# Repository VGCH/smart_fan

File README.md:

## Проект домашней автоматизации вытяжной вентиляции 

Принципиальная схема

Полное описание в статье на Хабр

[Ссылка на статью ](https://habr.com/ru/articles/823752/)

Если данный проект был вам полезен, то вы можете задонатить разработчику на кофе. 

[Ссылка на Boosty ](https://boosty.to/cyberex_tech)

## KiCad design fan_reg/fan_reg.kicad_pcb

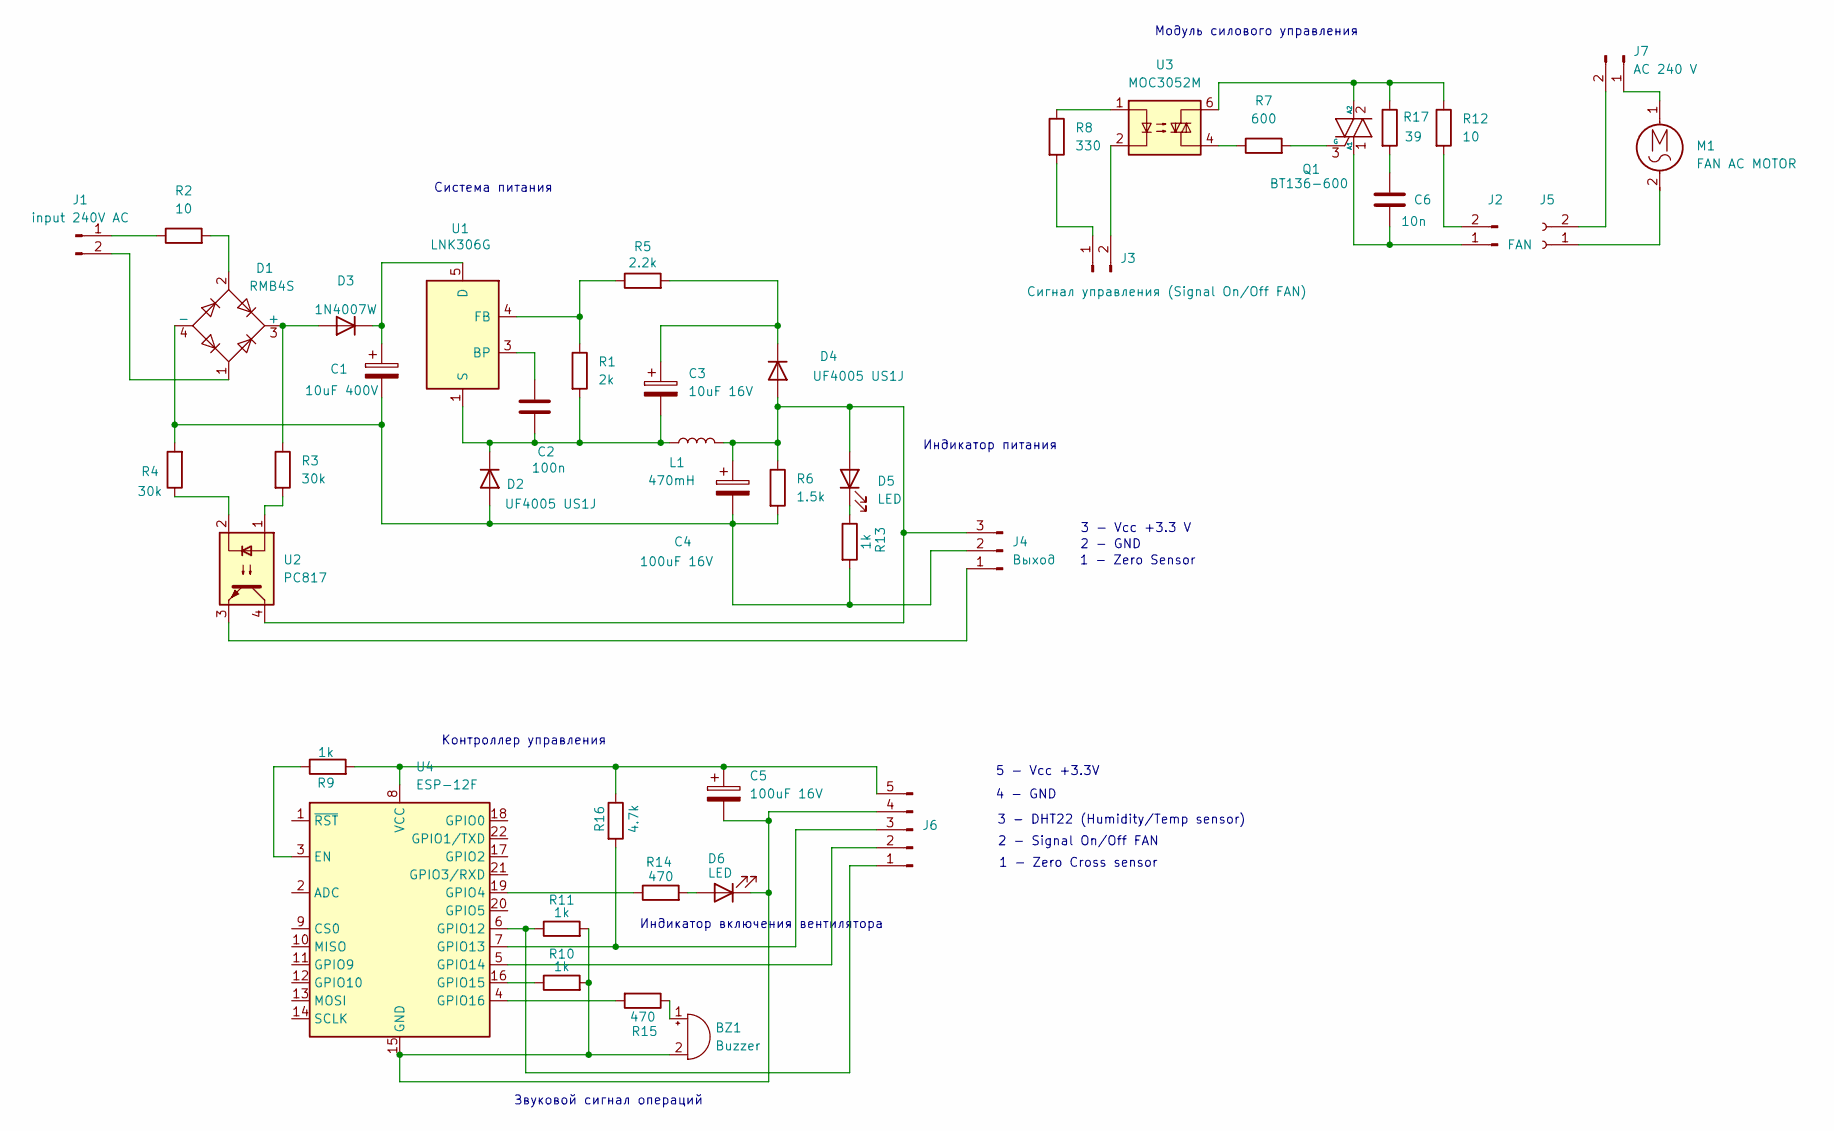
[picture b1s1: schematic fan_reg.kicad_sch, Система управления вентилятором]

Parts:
BZ1: Buzzer; MagneticBuzzer_PUI_AT-0927-TT-6-R
C1: 10uF 400V; CP_Radial_D8.0mm_P3.80mm
C2: 100n; C_1206_3216Metric
C3: 10uF 16V; CP_Elec_5x5.4
C4, C5: 100uF 16V; CP_Elec_5x5.4
C6: 10n; C_1206_3216Metric
D1: RMB4S; TO-269AA
D2, D4: UF4005 US1J; D_MELF
D3: 1N4007W; D_MELF
D5, D6: LED; LED_1206_3216Metric
J1: input 240V AC; TerminalBlock_bornier-2_P5.08mm
J2: FAN; TerminalBlock_bornier-2_P5.08mm
J3: Сигнал управления (Signal On/Off FAN); TerminalBlock_bornier-2_P5.08mm
J4: Выход; TerminalBlock_bornier-3_P5.08mm
J5: (no value)
J6: TerminalBlock_bornier-5_P5.08mm
J7: AC 240 V
L1: 470mH; L_Axial_L9.5mm_D4.0mm_P2.54mm_Vertical_Fastron_SMCC
M1: FAN AC MOTOR
Q1: BT136-600; TO-252-2
R1: 2k; R_0805_2012Metric
R2, R12: 10; R_1206_3216Metric
R3, R4: 30k; R_1206_3216Metric
R5: 2.2k; R_0805_2012Metric
R6: 1.5k; R_0805_2012Metric
R7: 600; R_0805_2012Metric
R8: 330; R_0805_2012Metric
R9, R10, R11, R13: 1k; R_0805_2012Metric
R14, R15: 470; R_0805_2012Metric
R16: 4.7k; R_0805_2012Metric
R17: 39; R_1206_3216Metric
U1: LNK306G; PowerIntegrations_SMD-8B
U2: PC817; Panasonic_APV-AQY_SSOP-4_4.45x2.65mm_P1.27mm
U3: MOC3052M; DIP-6_W7.62mm
U4: ESP-12F; ESP-12E

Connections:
unnamed: BZ1.1 (+), R15.1
unnamed: BZ1.2 (-), C5.2, D6.1 (K), J6.4, R10.2, R11.2, U4.15 (GND)
unnamed: C6.1, R17.2
unnamed: D1.3 (+), D3.2 (A), R3.1
unnamed: C1.2, C4.2, D1.4 (-), D2.2 (A), J4.2, R4.2, R6.2, R13.2
unnamed: D1.2, R2.2
unnamed: C2.1, C3.2, D2.1 (K), L1.1, R1.2, U1.1 (S), U1.2 (S), U1.7 (S), U1.8 (S)
unnamed: C1.1, D3.1 (K), U1.5 (D)
unnamed: C4.1, D4.2 (A), D5.2 (A), J4.3, L1.2, R6.1, U2.4
unnamed: C3.1, D4.1 (K), R5.2
unnamed: D5.1 (K), R13.1
unnamed: D6.2 (A), R14.2
unnamed: J1.1, R2.1
unnamed: D1.1, J1.2
unnamed: C6.2, J2.1, Q1.1 (A1)
unnamed: J2.2, R12.2
unnamed: J3.1, R8.2
unnamed: J3.2, U3.2
unnamed: J4.1, U2.3
unnamed: J5.1, M1.2
unnamed: J5.2, J7.2
unnamed: J6.1, R11.1, U4.6 (GPIO12)
unnamed: J6.2, U4.5 (GPIO14)
unnamed: J6.3, R16.2, U4.7 (GPIO13)
unnamed: C5.1, J6.5, R9.2, R16.1, U4.8 (VCC)
unnamed: J7.1, M1.1
unnamed: Q1.2 (A2), R12.1, R17.1, U3.6
unnamed: Q1.3 (G), R7.2
unnamed: R3.2, U2.1
unnamed: R4.1, U2.2
unnamed: R7.1, U3.4
unnamed: R8.1, U3.1
unnamed: C2.2, U1.3 (BP)
unnamed: R1.1, R5.1, U1.4 (FB)
unnamed: R9.1, U4.3 (EN)
unnamed: R14.1, U4.19 (GPIO4)
unnamed: R10.1, U4.16 (GPIO15)
unnamed: R15.2, U4.4 (GPIO16)

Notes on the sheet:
4 - GND
Индикатор включения вентилятора
Модуль силового управления
3 - DHT22 (Humidity/Temp sensor)
Контроллер управления
2 - GND
5 - Vcc +3.3V
1 - Zero Cross sensor
3 - Vcc +3.3 V
1 - Zero Sensor
2 - Signal On/Off FAN
Звуковой сигнал операций
Система питания
Индикатор питания

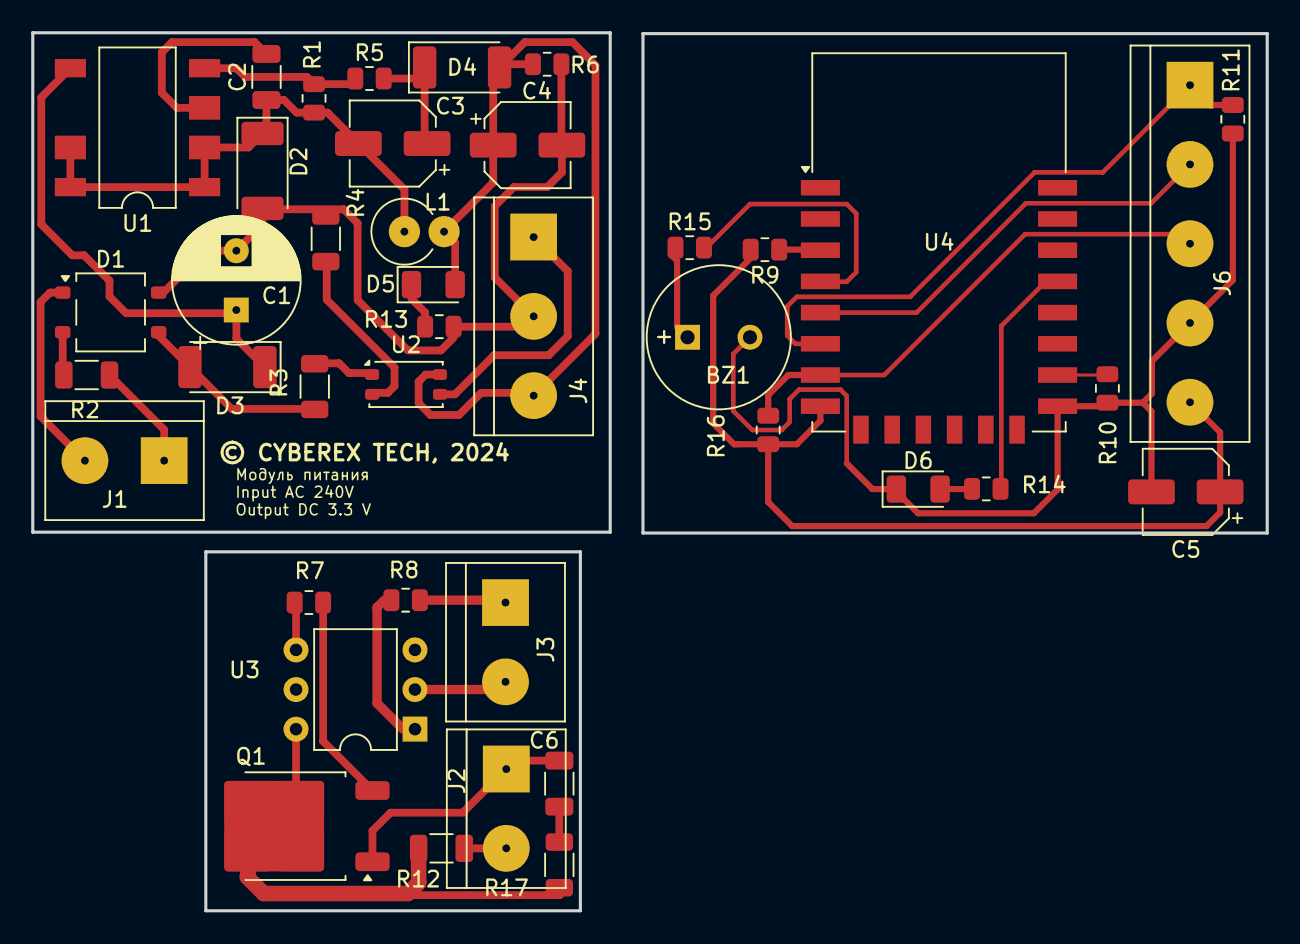
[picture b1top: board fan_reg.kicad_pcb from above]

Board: 2 copper layers, 79.1 x 56.3 mm, 41 parts (0 on the bottom side), 35 nets.

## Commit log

2024-07-03 fix bug
2024-07-03 Update README.md
    Update
2024-07-03 Delete fan_reg/fan_reg-backups directory
    Update

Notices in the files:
fan_reg/fan_reg.kicad_pcb:
© CYBEREX TECH, 2024
